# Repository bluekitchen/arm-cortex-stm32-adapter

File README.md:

# ARM Cortex STM32 Adapter

A simple adapter to connect STM32 development boards like the STM32 Nucleo or the STM32 Discovery boards to a JTAG/SWD tool like SEGGER's J-Link.

While ST Micro provides a firmware update that converts the built-in ST/Link program adapter in a J-Link, it's easier to just use your regular JTAG/SWD adapter without making any modification. 

The adapter can be directly plugged into the [20-pin JTAG interface](https://www.segger.com/products/debug-probes/j-link/technology/interface-description/).
. On the other side, the 6-pin header JP2 can be connected to the SWD interface of the STM32 board. Most JTAG/SWD tools requires a connection to the target VDD as well, which can be provided via JP3. Finally, the J-Link provides a 5V output, which can be used to power the dev board as well (please check documentation about how to configure this)

It is can be directly [ordered at OSHpark](https://oshpark.com/shared_projects/92vOWrue)

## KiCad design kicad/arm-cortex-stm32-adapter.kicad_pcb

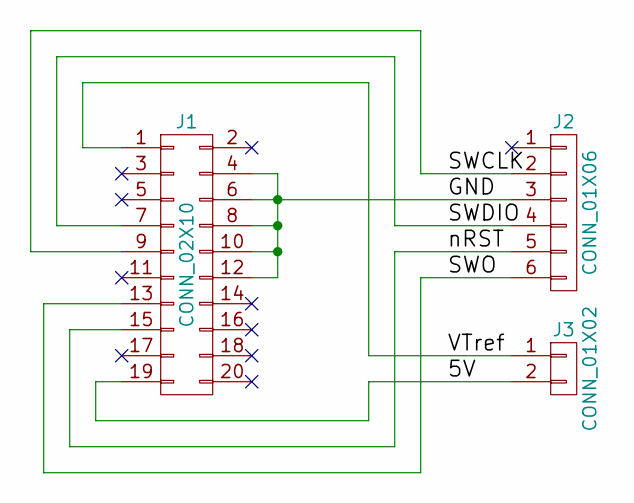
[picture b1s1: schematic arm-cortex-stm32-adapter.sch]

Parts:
J1: CONN_02X10; Pin_Header_Straight_2x10_Pitch2.54mm
J2: CONN_01X06; Pin_Header_Straight_1x06_Pitch2.54mm
J3: CONN_01X02; Pin_Header_Straight_1x02_Pitch2.54mm

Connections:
/5V: J1.19, J3.2
/GND: J1.4, J1.6, J1.8, J1.10, J1.12, J2.3
/SWCLK: J1.9, J2.2
/SWDIO: J1.7, J2.4
/SWO: J1.13, J2.6
/VTref: J1.1, J3.1
/nRST: J1.15, J2.5

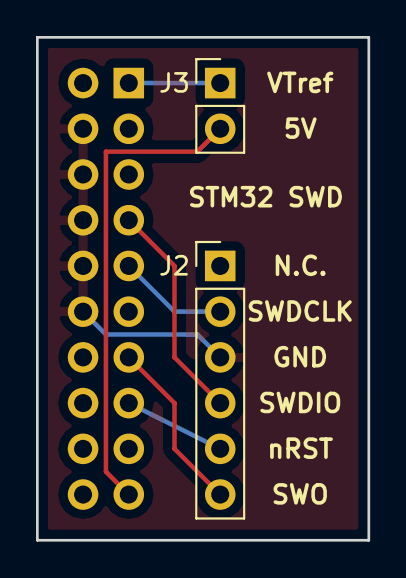
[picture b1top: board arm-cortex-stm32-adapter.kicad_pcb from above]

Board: 2 copper layers, 18.4 x 27.9 mm, 3 parts (1 on the bottom side), 7 nets.

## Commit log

2018-04-16 fix Oshpark link
